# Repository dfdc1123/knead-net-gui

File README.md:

# KneadNet

[English](README.md) | [简体中文](README.zh-CN.md)

> Knead what your nets need.

Schematic → breadboard

## Quick start

1. Install and launch KneadNet.
2. Select or drop a folder containing a KiCad project.
3. Choose a breadboard and bind the power rails.
4. Follow the schematic, breadboard view, and assembly checklist while building the circuit.

## Screenshots

### Import a KiCad project

### Choose a breadboard

### Compute a layout

### Use the assembly view

## Highlights 🌟

- Dark mode and high-DPI support
- Very small installer size
- Keyboard shortcuts

## Download

Download published builds from [GitHub Releases](https://github.com/dfdc1123/knead-net-gui/releases).

| Platform | Recommended file | Notes |
| --- | --- | --- |
| Windows x64 | `KneadNet_<version>_windows_x64-setup.exe` | Installer for most Windows users |
| Windows x64 | `KneadNet_<version>_windows_x64_en-US.msi` | MSI for managed environments |
| macOS Intel / Apple silicon | `KneadNet_<version>_macos_universal.dmg` | Universal application bundle |
| Linux x86-64 | `KneadNet_<version>_linux_amd64.AppImage` | Portable single-file application |
| Debian / Ubuntu x86-64 | `kneadnet_<version>_amd64.deb` | Debian package |
| Fedora / RPM x86-64 | `kneadnet-<version>-1.x86_64.rpm` | RPM package |

Releases also include `SHA256SUMS` for verifying downloads and the [`KneadNet-examples-0.2.5.zip` example archive](https://github.com/dfdc1123/knead-net-gui/releases/download/v0.2.5/KneadNet-examples-0.2.5.zip) for trying the application.

Current builds are not code-signed, so Windows SmartScreen or macOS Gatekeeper may show a warning. Only run files downloaded from this repository, and verify their SHA-256 checksum whenever possible.

An AppImage downloaded through a browser may not have executable permission. Enable it with:

```bash
chmod +x KneadNet_<version>_linux_amd64.AppImage
./KneadNet_<version>_linux_amd64.AppImage
```

Arch Linux users can install the binary package from the [AUR](https://aur.archlinux.org/packages/kneadnet-bin):

```bash
paru -S kneadnet-bin
```

The former `knead-net-gui` package belongs to the naming scheme used before v0.2.0; use `kneadnet-bin` for current releases.

## Example projects

The easiest option is to download the [`KneadNet-examples-0.2.5.zip` example archive](https://github.com/dfdc1123/knead-net-gui/releases/download/v0.2.5/KneadNet-examples-0.2.5.zip) from GitHub. Extract it, then open one of its project folders in KneadNet.

You can also browse the repository's [`examples/` directory](examples/). See [`examples/README.md`](examples/README.md) for the purpose of each example.

## Platform notes

- **Windows:** Tested and supported.
- **AUR:** Tested and supported.
- **Other platforms:** Not tested; feedback is welcome.

## Contributing

Bug reports and focused pull requests are welcome. Include the KneadNet version, operating system, package format, KiCad version, and reproduction steps. Attach a minimal project only when licensing and privacy allow it; never upload a private schematic without permission.

## License

KneadNet is released under the [GNU General Public License v3.0](LICENSE), identified as `GPL-3.0-only`.

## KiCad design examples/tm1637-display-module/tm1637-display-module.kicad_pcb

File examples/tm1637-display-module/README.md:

# TM1637 display module / TM1637 数码管模块

This KiCad project was converted from the GPL-3.0
[TM1637 display module published by `zhbaa`](https://oshwhub.com/zhbaa/tm1637-shu-ma-guan-mo-kuai)
on OSHWHub and normalized to the project name `tm1637-display-module`. KiCad
local history, nested Git metadata, lock files, and local preference files are
intentionally omitted.

All PCB component pads are through-hole. The project is kept as a manual
example and a regression fixture for physical footprint bounds. In particular,
`LED1` uses `Display_7Segment:CA56-12CGKWA`: its pins occupy a much smaller
area than the display body drawn on `F.Fab`. KneadNet must use the footprint
body outline for rendering and collision checks, with the pin extent only as a
fallback when no usable footprint graphics exist.

`H1` and `U4` use KiCad's standard vertical 1×4 through-hole pin-header
footprint. This supersedes the earlier imported copy that incorrectly used fan
header footprints for those connectors.

## 中文说明

该工程来自 `zhbaa` 在立创开源硬件平台以 GPL 3.0 发布的
[TM1637 数码管模块](https://oshwhub.com/zhbaa/tm1637-shu-ma-guan-mo-kuai)，
由嘉立创 EDA 转换为 KiCad 后将工程名统一为 `tm1637-display-module`。本地历史、
嵌套 Git 数据、锁文件和本机偏好文件不纳入示例。

PCB 中的元件焊盘均为直插。该工程既用于手动测试，也用于封装物理边界回归测试。尤其是
`LED1` 使用 `Display_7Segment:CA56-12CGKWA`：引脚覆盖范围远小于 `F.Fab`
层描述的数码管本体。KneadNet 应使用封装本体外形进行渲染和碰撞检测，只有在找不到可用
封装图形时才回退到引脚范围。

`H1` 和 `U4` 现使用 KiCad 标准的 1×4、2.54 mm 直插排针封装，取代了早期导入版本中
不正确的风扇排针封装。

## License / 许可证

The imported project remains attributed to `zhbaa` and distributed under the
upstream project's stated GPL 3.0 license.

导入工程保留对原作者 `zhbaa` 的署名，并遵循原项目标明的 GPL 3.0 许可证。

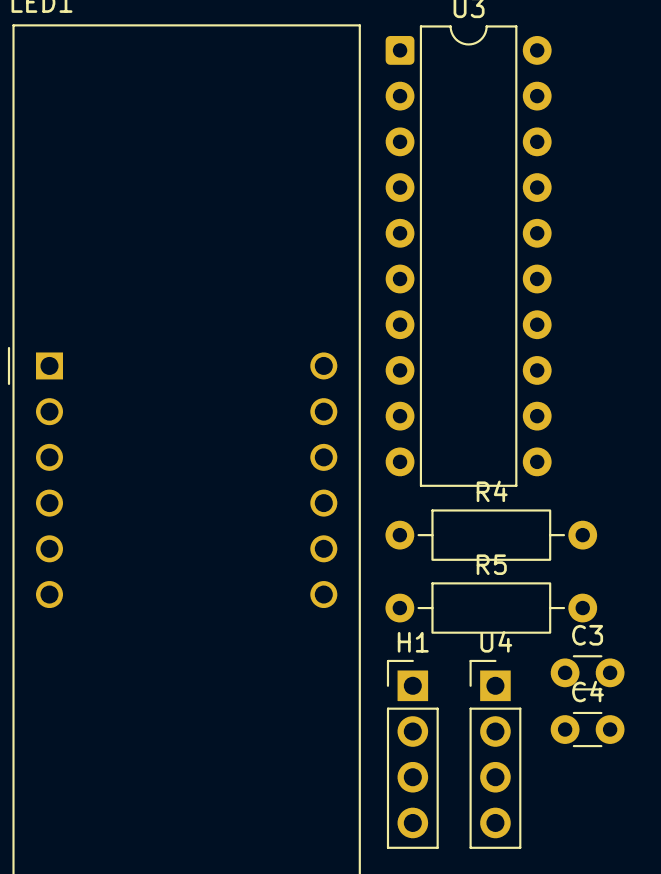
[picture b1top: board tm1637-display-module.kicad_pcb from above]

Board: 2 copper layers, 8 parts (0 on the bottom side), 16 nets, no tracks yet.

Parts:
C3, C4: 100pF; C_Disc_D3.0mm_W1.6mm_P2.50mm
H1: PinHeader_1x04_P2.54mm_Vertical
LED1: CA56-12CGKWA
R4, R5: 10K; R_Axial_DIN0207_L6.3mm_D2.5mm_P10.16mm_Horizontal
U3: DIP-20_W7.62mm
U4: PinHeader_1x04_P2.54mm_Vertical

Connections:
+5V: H1.4, R4.2, R5.2, U3.16 (VDD), U4.4
/A: LED1.11 (A), U3.2 (SEG1/KS1)
/A1: LED1.12 (DIG1), U3.15 (GRID1)
/A2: LED1.9 (DIG2), U3.14 (GRID2)
/A3: LED1.8 (DIG3), U3.13 (GRID3)
/A4: LED1.6 (DIG4), U3.12 (GRID4)
/B: LED1.7 (B), U3.3 (SEG2/KS2)
/C: LED1.4 (C), U3.4 (SEG3/KS3)
/CLK: C3.2, H1.3, R5.1, U3.18 (CLK), U4.3
/D: LED1.2 (D), U3.5 (SEG4/KS4)
/DIO: C4.2, H1.2, R4.1, U3.17 (DIO), U4.2
/DP: LED1.3 (DP), U3.9 (SEG8/KS8)
/E: LED1.1 (E), U3.6 (SEG5/KS5)
/F: LED1.10 (F), U3.7 (SEG6/KS6)
/G: LED1.5 (G), U3.8 (SEG7/KS7)
GND: C3.1, C4.1, H1.1, U3.1 (GND), U4.1

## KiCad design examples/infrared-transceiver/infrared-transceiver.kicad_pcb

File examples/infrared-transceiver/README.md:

# Infrared transceiver / 红外发射接收模块

This directory contains a KiCad export of the open-source hardware project
[红外发射接收模块_2026-06-08_16-19-02](https://oshwhub.com/xindingsheng/project_xbshrerd)
by [芯鼎盛-硬件吴工 (`xindingsheng`)](https://oshwhub.com/xindingsheng).
The upstream project describes an infrared wireless communication module and
is published under the GPL 3.0 license.

The imported directory and KiCad project have been renamed to
`infrared-transceiver`. KiCad local-history data, nested Git metadata, lock
files, and local preference files are intentionally not included; the
schematic, PCB, project file, symbol library, and symbol-library table are
retained.

## KneadNet compatibility

The PCB footprints were converted from the upstream SMD defaults to THT
footprints on 2026-07-27. This version can be imported into KneadNet and is
also used to cover KiCad root-sheet local-label handling: the schematic label
`TX` corresponds to the canonical PCB net name `/TX`.

The footprint substitutions are examples, not manufacturing recommendations.
Before building the circuit, verify every selected package, pin number,
orientation, and physical part against its datasheet.

## Why KiCad shows `1111`

`1111` is not generated by KneadNet. It is the `Reference` of the imported
`Drawing-Symbol_A4` schematic symbol, which draws the decorative EasyEDA page
frame. The imported symbol has an empty reference prefix and is incorrectly
marked as a BOM/board item, so KiCad assigned it the numeric reference `1111`
and includes it in the footprint-assignment list. It has no electrical role
and no PCB footprint. If the drawing frame is not needed, it can be removed;
alternatively, exclude that symbol from the BOM and board.

## 中文说明

本目录来自开源硬件项目
[红外发射接收模块_2026-06-08_16-19-02](https://oshwhub.com/xindingsheng/project_xbshrerd)，
原作者为[芯鼎盛-硬件吴工（`xindingsheng`）](https://oshwhub.com/xindingsheng)，
上游页面标注的开源协议为 GPL 3.0。

仓库中的 PCB 已于 2026-07-27 从上游默认贴片封装转换为直插封装，现在可以导入
KneadNet。它也用于覆盖 KiCad 根层级局部标签的回归场景：原理图标签 `TX` 在 PCB 中的
规范网络名是 `/TX`。这些封装替换只是示例，并非生产建议；实际搭建前仍须根据数据手册
核对每个封装、引脚编号、方向和实物。

KiCad 封装选择界面中的 `1111` 不是 KneadNet 生成的。它是 EasyEDA 导入工程里的
`Drawing-Symbol_A4` 装饰性图框符号的位号。该符号的位号前缀为空，又被错误标记成参与
BOM 和 PCB，KiCad 因而给它分配了纯数字位号 `1111` 并列入封装选择。它没有电气作用，
也没有 PCB 封装；不需要图框时可以删除，或者在符号属性中将其排除出 BOM 和 PCB。

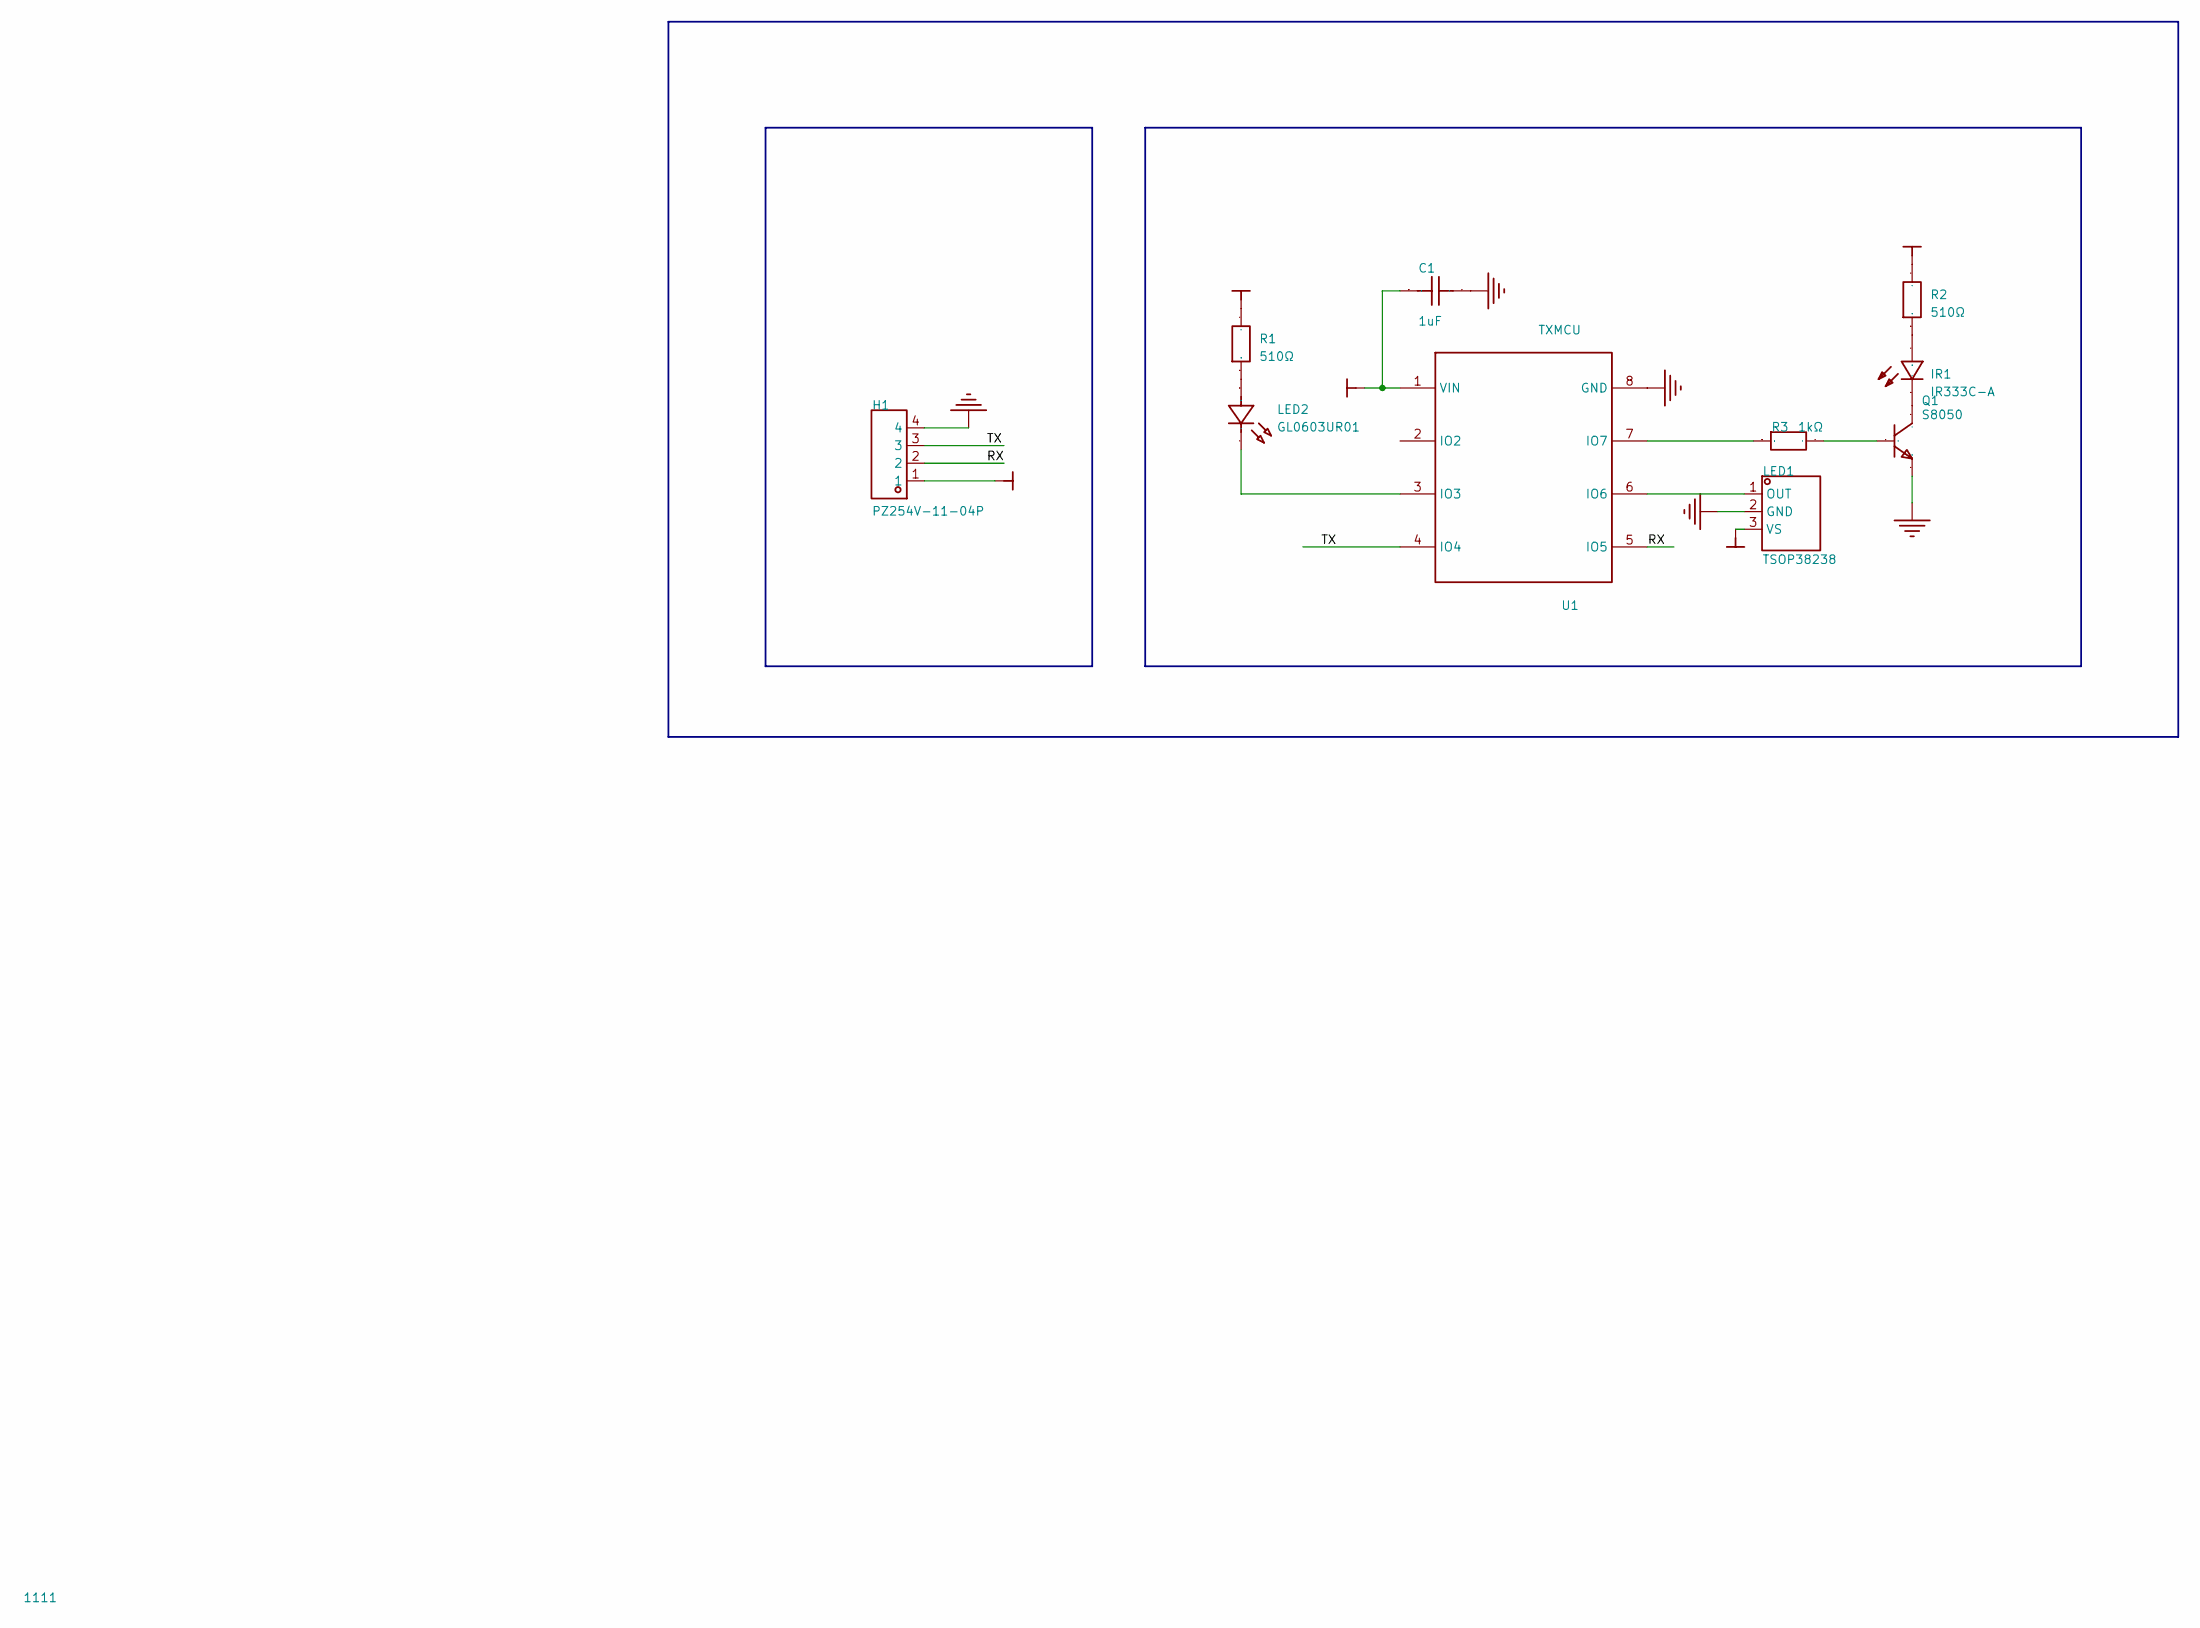
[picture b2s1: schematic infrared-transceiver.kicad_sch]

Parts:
1111: (no value)
C1: 1uF; C_Disc_D3.0mm_W1.6mm_P2.50mm; Manufacturer Part GRM188R71H104KA93D; LCSC Part Name 100nF ±10% 50V
H1: PZ254V-11-04P; FanPinHeader_1x04_P2.54mm_Vertical; Manufacturer Part PZ254V-11-04P; LCSC Part Name 1x4P 间距:2.54mm 方针 直插
IR1: IR333C-A; LED_D5.0mm; Manufacturer Part IR333C-A; LCSC Part Name Q档 IR333C-A
LED1: TSOP38238; LED_D5.0mm-3; Manufacturer Part TSOP38238; LCSC Part Name 接收距离45m ±45°
LED2: GL0603UR01; LED_D5.0mm; Manufacturer Part GL0603UR01; LCSC Part Name 0603 红灯 高亮
Q1: S8050; TO-92L_Inline_Wide; Manufacturer Part S8050; LCSC Part Name hFE:200-350，丝印:J3Y NPN 500mA 25V
R1: 510Ω; R_Axial_DIN0207_L6.3mm_D2.5mm_P10.16mm_Horizontal; Tolerance ±5%; Voltage-Supply(Max) 75V; Manufacturer Part FRC0603J511 TS; LCSC Part Name 510Ω ±5% 100mW 厚膜电阻
R2: 510Ω; R_Axial_DIN0207_L6.3mm_D2.5mm_P10.16mm_Horizontal; Manufacturer Part FRC0603J511 TS; LCSC Part Name 510Ω ±5% 100mW 厚膜电阻
R3: 1kΩ; R_Axial_DIN0207_L6.3mm_D2.5mm_P10.16mm_Horizontal; Tolerance ±5%; Voltage-Supply(Max) 75V; Manufacturer Part FRC0603J511 TS; LCSC Part Name 510Ω ±5% 100mW 厚膜电阻
U1: TXMCU; CERDIP-8_W7.62mm_SideBrazed; Manufacturer Part TXMCU; LCSC Part Name 8位微控制器 单片机 PY32F002AL15S6TU

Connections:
/RX: H1.2, U1.5 (IO5)
/TX: H1.3, U1.4 (IO4)
GND: C1.2, H1.4, LED1.2 (GND), Q1.2 (E), U1.8 (GND)
unnamed: IR1.2 (A), R2.1
unnamed: IR1.1 (C), Q1.3 (C)
unnamed: LED1.1 (OUT), U1.6 (IO6)
unnamed: LED2.1 (A), R1.1
unnamed: LED2.2 (C), U1.3 (IO3)
unnamed: Q1.1 (B), R3.2
unnamed: R3.1, U1.7 (IO7)
VCC: C1.1, H1.1, LED1.3 (VS), R1.2, R2.2, U1.1 (VIN)

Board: 2 copper layers, 10 parts (0 on the bottom side), 11 nets, no tracks yet.

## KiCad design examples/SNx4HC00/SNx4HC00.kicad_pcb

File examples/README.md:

# KneadNet example projects

These KiCad projects are provided for learning the KneadNet workflow and for manual smoke testing. Select an individual project directory—not the parent `examples/` directory—when opening it in KneadNet.

| Directory | Contents | Release bundle |
| --- | --- | --- |
| `NE555+CD4017/` | Developer fixture for schematic rendering tests | No |
| `SNx4HC00/` | KiCad project using an SNx4HC00 device | Yes |
| `h-bridge/` | H-bridge KiCad project | Yes |
| `lm741/` | LM741 KiCad project | Yes |
| `h-bridge_different_order/` | Developer fixture for component-order regression tests | No |
| `tm1637-display-module/` | THT TM1637 display fixture with an oversized seven-segment body | No |

Each public project includes `.kicad_pro`, `.kicad_sch`, and `.kicad_pcb` files. KneadNet requires the PCB file; the same-name schematic provides the preview and cross-selection.

Generated layouts are suggestions. Verify component orientation, pin numbering, power rails, and every connection before applying power.

## 中文说明

这些 KiCad 工程用于学习 KneadNet 的操作流程和手动烟测。在 KneadNet 中应选择某个具体工程文件夹，而不是父级 `examples/` 目录。

`SNx4HC00`、`h-bridge` 和 `lm741` 会进入 Release 示例包。`NE555+CD4017`
用于验证 NE555 特有的上划线、共享电源引脚和引脚文字渲染；
`h-bridge_different_order` 用于验证改变元件迭代顺序不会改变布局成本。
这两个目录都是开发测试夹具，不作为面向用户的示例发布。

`tm1637-display-module` 是一个直插 TM1637 数码管工程，同时用于验证元件占位框来自 KiCad
封装的物理外形，而不只是最外圈引脚。它来自 `zhbaa` 以 GPL 3.0 发布的
[TM1637 数码管模块](https://oshwhub.com/zhbaa/tm1637-shu-ma-guan-mo-kuai)。请参阅
[`tm1637-display-module/README.md`](tm1637-display-module/README.md)。

通电前必须人工检查元件方向、引脚编号、电源轨和每一条连接。

## License

KneadNet-authored examples are distributed under [`GPL-3.0-only`](../LICENSE).
The imported `tm1637-display-module` example remains attributed to `zhbaa`
under its upstream GPL 3.0 license.

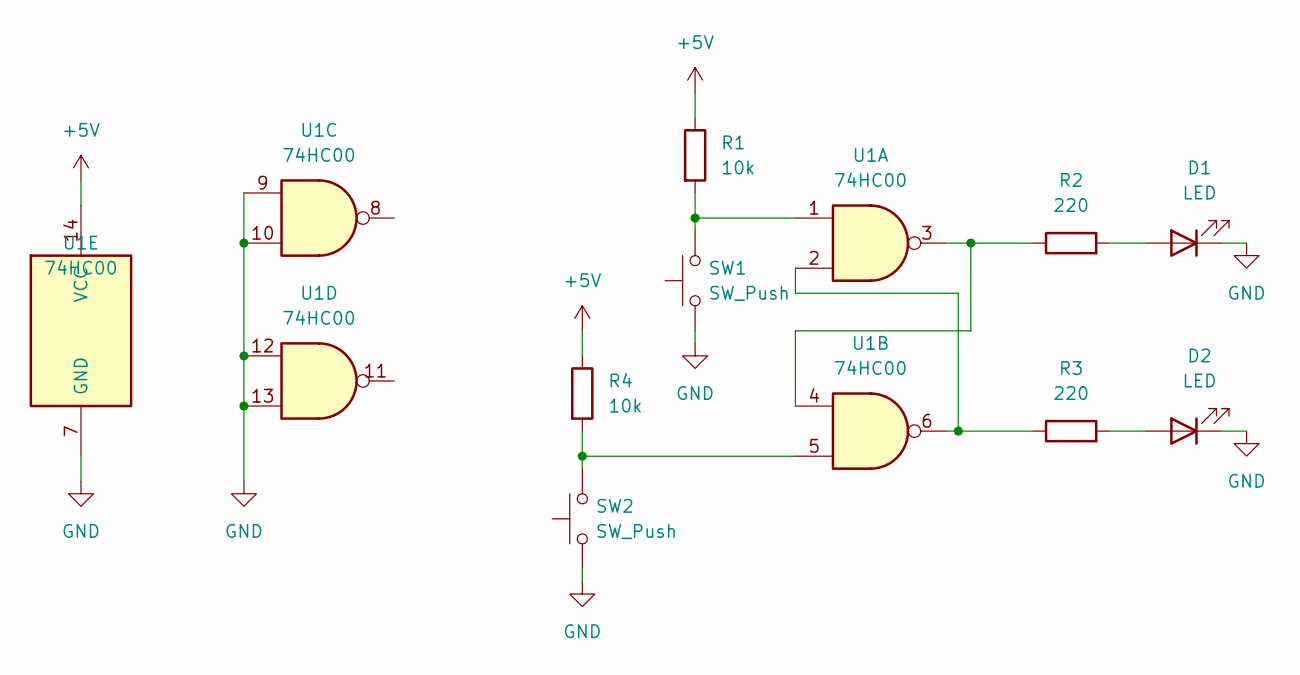
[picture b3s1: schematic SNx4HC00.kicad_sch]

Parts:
D1, D2: LED; LED_D5.0mm
R1, R4: 10k; R_Axial_DIN0207_L6.3mm_D2.5mm_P10.16mm_Horizontal
R2, R3: 220; R_Axial_DIN0207_L6.3mm_D2.5mm_P10.16mm_Horizontal
SW1, SW2: SW_Push; SW_PUSH_6mm
U1: 74HC00; DIP-14_W7.62mm

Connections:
+5V: R1.1, R4.1, U1.14 (VCC)
GND: D1.1 (K), D2.1 (K), SW1.1, SW2.1, U1.7 (GND), U1.9, U1.10, U1.12, U1.13
unnamed: D1.2 (A), R2.2
unnamed: D2.2 (A), R3.2
unnamed: R1.2, SW1.2, U1.1
unnamed: R2.1, U1.3, U1.4
unnamed: R3.1, U1.2, U1.6
unnamed: R4.2, SW2.2, U1.5

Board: 2 copper layers, 9 parts (0 on the bottom side), 8 nets, no tracks yet.

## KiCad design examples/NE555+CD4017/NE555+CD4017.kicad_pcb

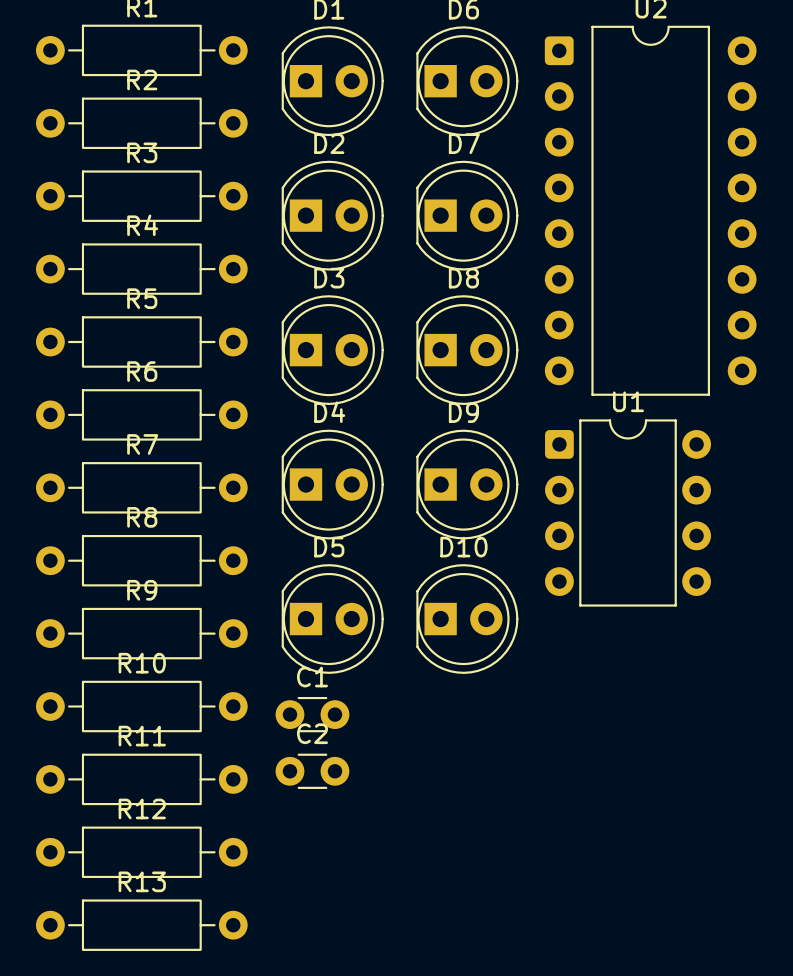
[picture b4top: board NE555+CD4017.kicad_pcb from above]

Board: 2 copper layers, 27 parts (0 on the bottom side), 26 nets, no tracks yet.

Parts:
C1, C2: 1uF; C_Disc_D3.0mm_W1.6mm_P2.50mm
D1, D2, D3, D4, D5, D6, D7, D8, D9, D10: LED; LED_D5.0mm
R1: 2.2k; R_Axial_DIN0207_L6.3mm_D2.5mm_P10.16mm_Horizontal
R2: 10k; R_Axial_DIN0207_L6.3mm_D2.5mm_P10.16mm_Horizontal
R3: 50k; R_Axial_DIN0207_L6.3mm_D2.5mm_P10.16mm_Horizontal
R4, R5, R6, R7, R8, R9, R10, R11, R12, R13: 1k; R_Axial_DIN0207_L6.3mm_D2.5mm_P10.16mm_Horizontal
U1: NE555P; DIP-8_W7.62mm
U2: 4017; DIP-16_W10.16mm

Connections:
GND: C1.2, C2.2, D1.1 (K), D2.1 (K), D3.1 (K), D4.1 (K), D5.1 (K), D6.1 (K), D7.1 (K), D8.1 (K), D9.1 (K), D10.1 (K), U1.1 (GND), U2.8 (VSS), U2.13 (CKEN), U2.15 (Reset)
unnamed: D1.2 (A), R4.2
unnamed: D2.2 (A), R5.2
unnamed: D3.2 (A), R6.2
unnamed: D4.2 (A), R7.2
unnamed: D5.2 (A), R8.2
unnamed: D6.2 (A), R9.2
unnamed: D7.2 (A), R10.2
unnamed: D8.2 (A), R11.2
unnamed: D9.2 (A), R12.2
unnamed: D10.2 (A), R13.2
unnamed: R2.2, R3.1
unnamed: R1.2, R2.1, U1.7 (DISCH)
unnamed: U1.3 (OUT), U2.14 (CLK)
unnamed: C1.1, R3.2, U1.2 (TRIG), U1.6 (THRES)
unnamed: R4.1, U2.3 (Q0)
unnamed: R5.1, U2.2 (Q1)
unnamed: R6.1, U2.4 (Q2)
unnamed: R7.1, U2.7 (Q3)
unnamed: R8.1, U2.10 (Q4)
unnamed: R9.1, U2.1 (Q5)
unnamed: R10.1, U2.5 (Q6)
unnamed: R11.1, U2.6 (Q7)
unnamed: R12.1, U2.9 (Q8)
unnamed: R13.1, U2.11 (Q9)
VCC: C2.1, R1.1, U1.4 (~RST), U1.8 (VCC), U2.16 (VDD)

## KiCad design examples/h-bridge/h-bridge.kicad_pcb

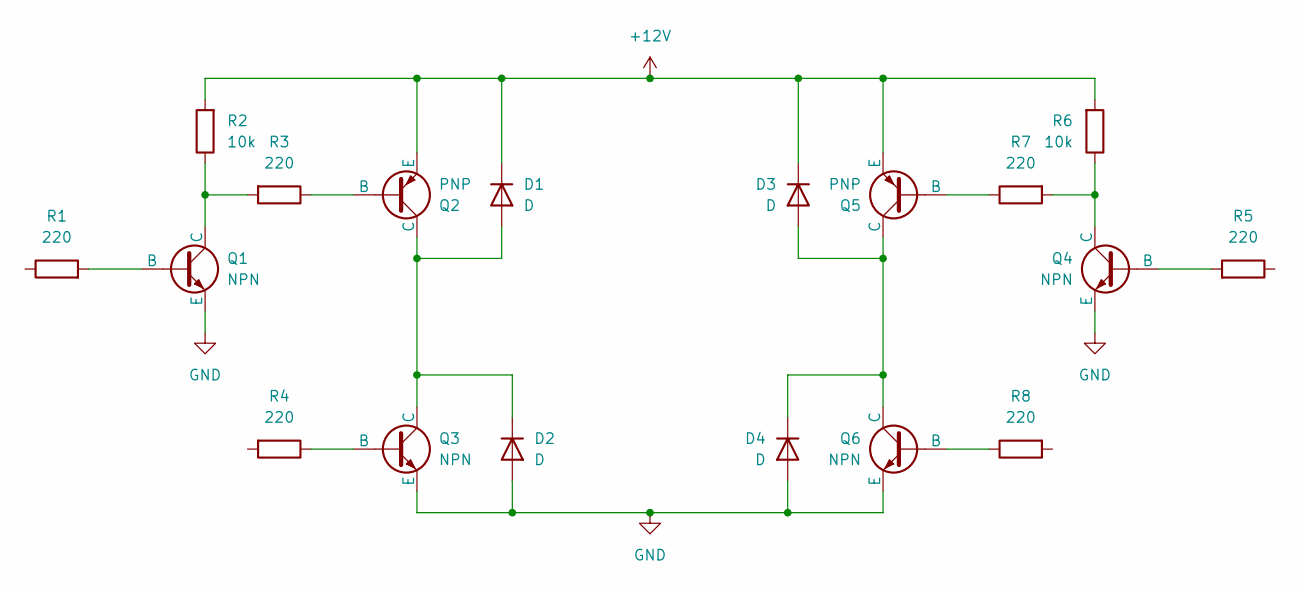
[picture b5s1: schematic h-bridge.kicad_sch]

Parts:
D1, D2, D3, D4: D; D_DO-41_SOD81_P10.16mm_Horizontal
Q1, Q3, Q4, Q6: NPN; TO-92L_Inline_Wide
Q2, Q5: PNP; TO-92L_Inline_Wide
R1, R3, R4, R5, R7, R8: 220; R_Axial_DIN0207_L6.3mm_D2.5mm_P10.16mm_Horizontal
R2, R6: 10k; R_Axial_DIN0207_L6.3mm_D2.5mm_P10.16mm_Horizontal

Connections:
+12V: D1.1 (K), D3.1 (K), Q2.3 (E), Q5.3 (E), R2.2, R6.2
GND: D2.2 (A), D4.2 (A), Q1.3 (E), Q3.3 (E), Q4.3 (E), Q6.3 (E)
unnamed: D1.2 (A), D2.1 (K), Q2.1 (C), Q3.1 (C)
unnamed: D3.2 (A), D4.1 (K), Q5.1 (C), Q6.1 (C)
unnamed: Q1.2 (B), R1.2
unnamed: Q1.1 (C), R2.1, R3.2
unnamed: Q2.2 (B), R3.1
unnamed: Q3.2 (B), R4.1
unnamed: Q4.2 (B), R5.2
unnamed: Q4.1 (C), R6.1, R7.2
unnamed: Q5.2 (B), R7.1
unnamed: Q6.2 (B), R8.1

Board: 2 copper layers, 18 parts (0 on the bottom side), 12 nets, no tracks yet.

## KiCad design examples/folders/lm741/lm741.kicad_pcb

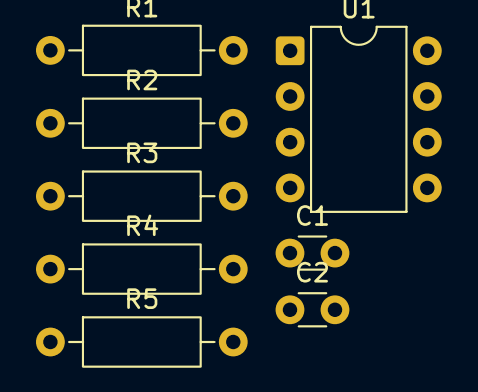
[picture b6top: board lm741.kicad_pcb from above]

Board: 2 copper layers, 8 parts (0 on the bottom side), 3 nets, no tracks yet.

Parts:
C1, C2: C; C_Disc_D3.0mm_W1.6mm_P2.50mm
R1, R2, R3, R4, R5: R; R_Axial_DIN0207_L6.3mm_D2.5mm_P10.16mm_Horizontal
U1: LM741; DIP-8_W7.62mm

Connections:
unnamed: C1.2, R1.2, U1.6
unnamed: C2.1, R5.2
unnamed: C1.1, C2.2, R1.1, R2.2, R3.2, R4.2, U1.2 (-)

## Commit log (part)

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2026-06-22 Initialize knead-net project
    Set up Rust crate for parsing circuit netlists from JSON,
    with serde-based input types and an example LED-BJT circuit.
2026-06-22 refactor: rename variables for readability
2026-06-22 feat: convert CircuitInput to Circuit
2026-06-24 refactor: circuit input
2026-06-24 feat: read from .net
    file from kicad
2026-06-24 feat: add pinfunction refactor: rename Component:name
2026-06-24 feat: breadboard defined
2026-06-24 fix: wire definition
2026-06-24 feat: place_row
2026-06-25 feat: PathFinder
2026-06-25 feat: colorfull wires
2026-06-25 feat: Simulated Annealing
2026-06-25 feat: force directed
2026-06-25 fix: short circuit
2026-06-25 fix: overlap
2026-06-25 feat: better breadboard
2026-06-25 feat: use mst replace hpwl
2026-06-25 refactor: using fastrand
2026-06-25 refactor: using compactness instead of compact
2026-06-25 feat: better SA
2026-06-26 fix: start SA without 1M cost
2026-06-26 docs: typo
2026-06-26 feat: power rail
2026-06-26 feat: wire with power rail
2026-06-26 feat: bridgeable
2026-06-26 feat: bridge components
2026-06-26 fix: auto bridge components
2026-06-26 refactor: naming for MST
2026-06-26 feat: higher weights for mst
2026-06-26 fix: breadboard power rail generator
